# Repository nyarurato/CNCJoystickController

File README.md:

# CNCJoystickController
CNC Joystick Controller for RepRap Firmware Duet3

Using in 
https://bbs.avalontech.jp/t/topic/1473

# DEMO

from: https://twitter.com/Gymnopedian/status/1694639996589015279

# Licence
## Hardware
[CC BY-SA 4.0](https://creativecommons.org/licenses/by-sa/4.0/)

## Software
[GPLv3](https://www.gnu.org/licenses/gpl-3.0.html)

Software is forked from https://github.com/Duet3D/CNC-Pendant-Firmware

# Author
[nyaruarto](https://github.com/nyarurato)

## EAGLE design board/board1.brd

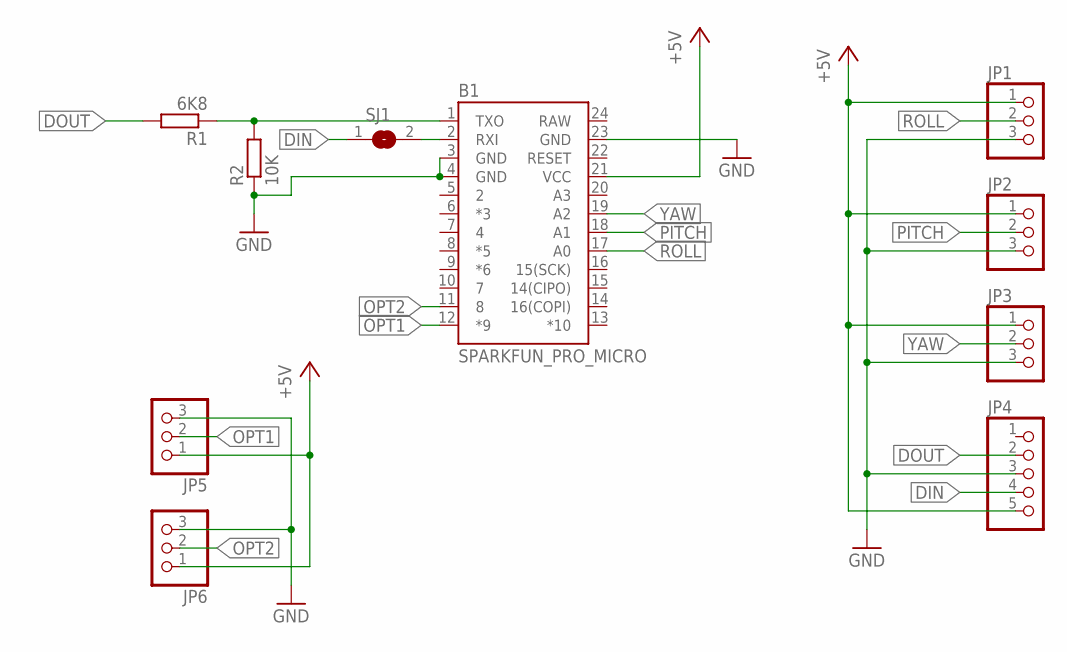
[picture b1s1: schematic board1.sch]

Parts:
B1: SPARKFUN_PRO_MICRO
JP1, JP2, JP3, JP5, JP6: PINHD-1X3; 1X03
JP4: PINHD-1X5; 1X05
R1: 6K8; R0603
R2: 10K; R0603
SJ1: SJ

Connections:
+5V: B1.21 (VCC), JP1.1, JP2.1, JP3.1, JP4.5, JP5.1, JP6.1
DIN: JP4.4, SJ1.1
DOUT: JP4.2, R1.2
GND: B1.3 (GND), B1.4 (GND), B1.23 (GND), JP1.3, JP2.3, JP3.3, JP4.3, JP5.3, JP6.3, R2.1
unnamed: B1.1 (TXO), R1.1, R2.2
unnamed: B1.2 (RXI), SJ1.2
OPT1: B1.12 (*9), JP5.2
OPT2: B1.11 (8), JP6.2
PITCH: B1.18 (A1), JP2.2
RAW: B1.24 (RAW)
ROLL: B1.17 (A0), JP1.2
YAW: B1.19 (A2), JP3.2

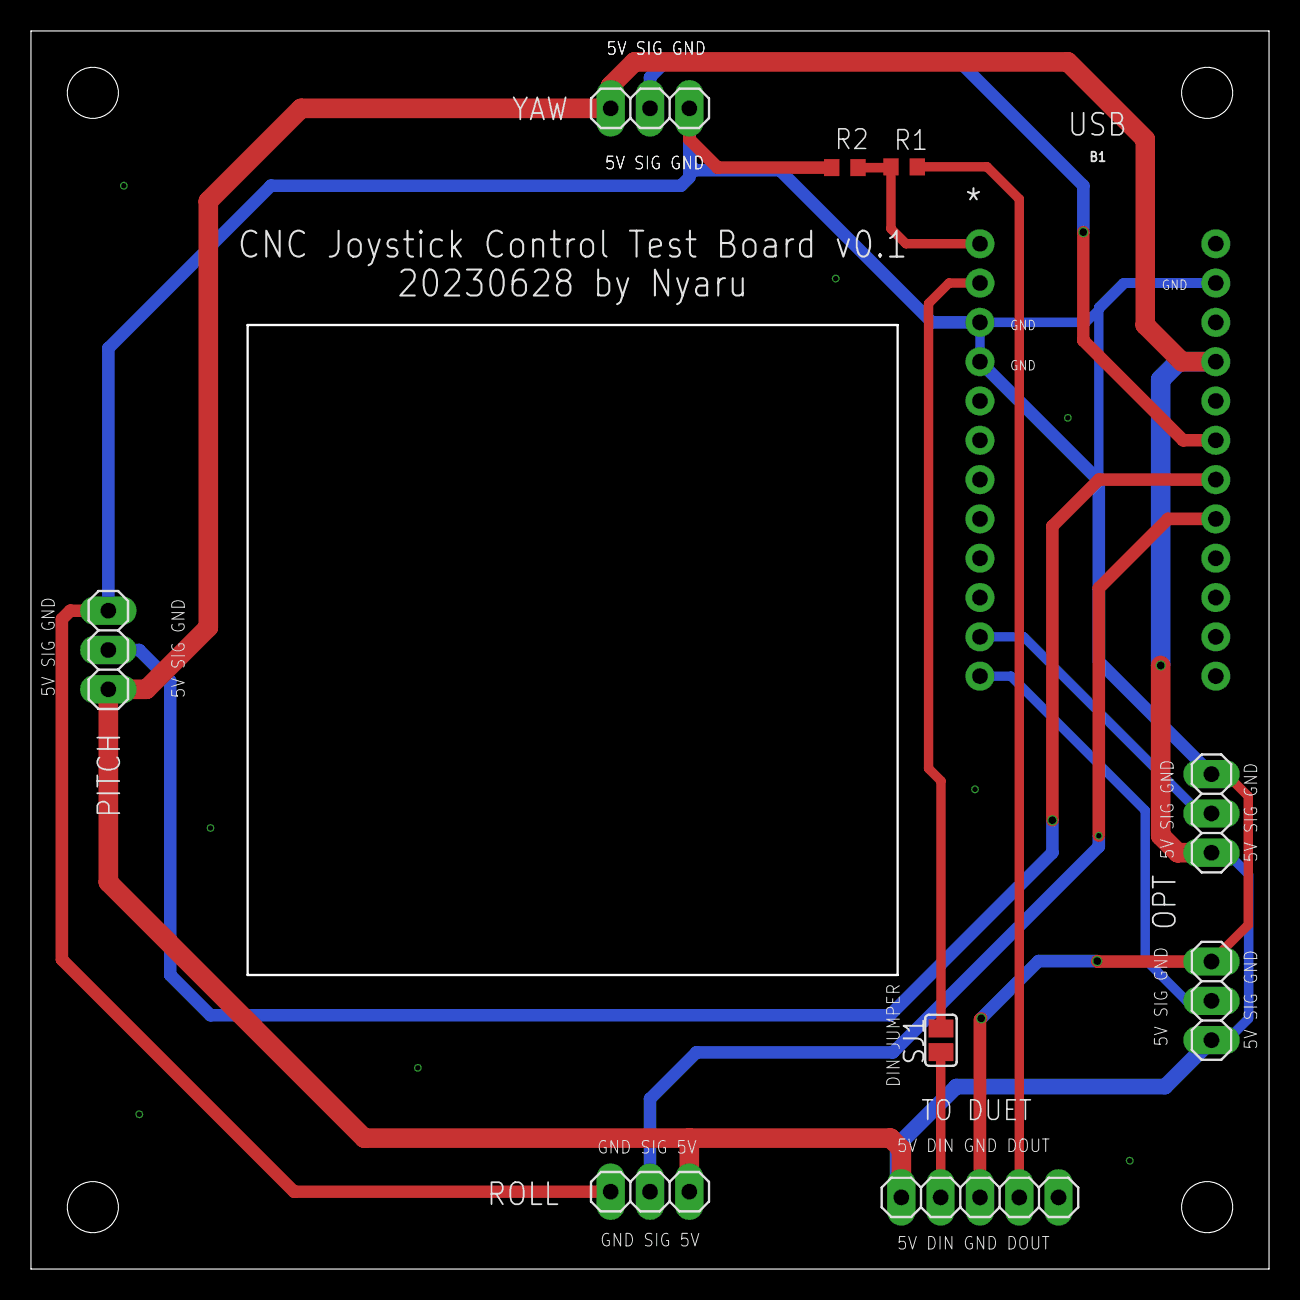
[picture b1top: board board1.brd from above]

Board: 2 copper layers, 80.0 x 80.0 mm, 10 parts (0 on the bottom side), 11 nets.

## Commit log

2023-08-27 upload board files
2023-08-27 change License
2023-08-27 upload image
2023-08-27 upload software codes
2023-08-27 update license

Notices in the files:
parts and their libraries:
SparkFun-Boards: Licensing: Creative Commons ShareAlike 4.0 International - https://creativecommons.org/licenses/by-sa/4.0
